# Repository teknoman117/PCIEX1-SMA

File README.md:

# PCIEX1-SMA

Adapts a PCIe x1 slot into 6 SMA connectors (REFCLK, TX, and RX differential pairs), and a pin header for SMBUS and the PERST signal. This is intended to be the one of the lowest cost SMA adapter boards for PCIe x1.

Imagined use case is adapting the Crosslink-NX Evaluation Board into a PCIe capable board by installing the missing SMA connectors and providing an adapter board to an actual PCIe connector.

## License

CC-BY-SA 4.0

## Assembled

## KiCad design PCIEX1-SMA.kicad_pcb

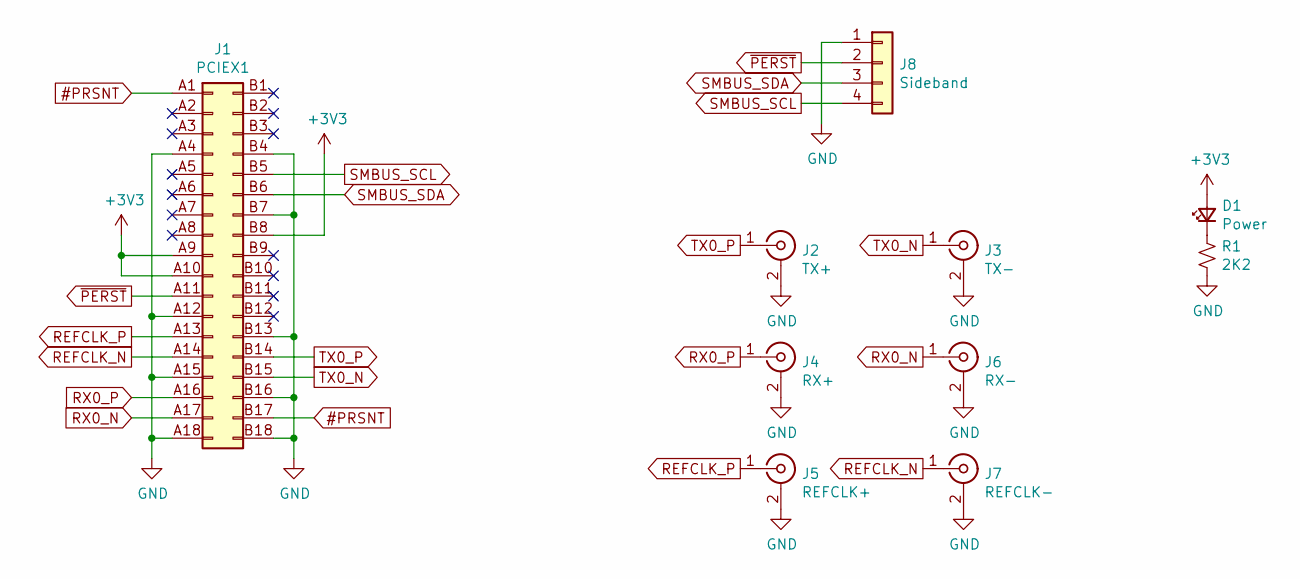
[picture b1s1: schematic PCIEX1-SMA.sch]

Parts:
D1: Power; LED_0603_1608Metric_Pad1.05x0.95mm_HandSolder; Mouser_PN 743-S63BTR
J1: PCIEX1; BUS_PCIexpress_x1
J2: TX+; SMA_Amphenol_132134_Vertical; Mouser_PN 538-73391-0060
J3: TX-; SMA_Amphenol_132134_Vertical
J4: RX+; SMA_Amphenol_132134_Vertical
J5: REFCLK+; SMA_Amphenol_132134_Vertical
J6: RX-; SMA_Amphenol_132134_Vertical
J7: REFCLK-; SMA_Amphenol_132134_Vertical
J8: Sideband; PinHeader_1x04_P2.54mm_Vertical; Mouser_PN 538-42375-2523
R1: 2K2; R_0603_1608Metric_Pad0.98x0.95mm_HandSolder; Mouser_PN 652-CR0603FX-2201ELF

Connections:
#PRSNT: J1.A1 (Pin_a1), J1.B17 (Pin_b17)
+3V3: D1.2 (A), J1.A9 (Pin_a9), J1.A10 (Pin_a10), J1.B8 (Pin_b8)
GND: J1.A4 (Pin_a4), J1.A12 (Pin_a12), J1.A15 (Pin_a15), J1.A18 (Pin_a18), J1.B4 (Pin_b4), J1.B7 (Pin_b7), J1.B13 (Pin_b13), J1.B16 (Pin_b16), J1.B18 (Pin_b18), J2.2 (Ext), J3.2 (Ext), J4.2 (Ext), J5.2 (Ext), J6.2 (Ext), J7.2 (Ext), J8.1, R1.2
unnamed: D1.1 (K), R1.1
REFCLK_N: J1.A14 (Pin_a14), J7.1 (In)
REFCLK_P: J1.A13 (Pin_a13), J5.1 (In)
RX0_N: J1.A17 (Pin_a17), J6.1 (In)
RX0_P: J1.A16 (Pin_a16), J4.1 (In)
SMBUS_SCL: J1.B5 (Pin_b5), J8.4
SMBUS_SDA: J1.B6 (Pin_b6), J8.3
TX0_N: J1.B15 (Pin_b15), J3.1 (In)
TX0_P: J1.B14 (Pin_b14), J2.1 (In)
~PERST: J1.A11 (Pin_a11), J8.2

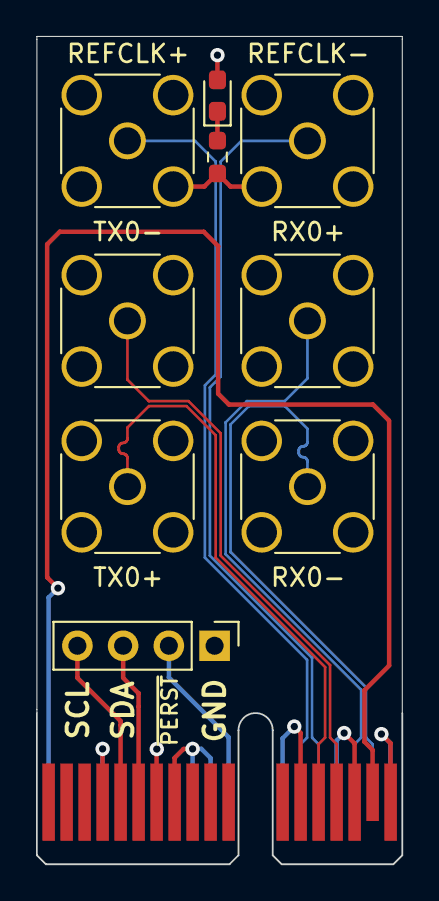
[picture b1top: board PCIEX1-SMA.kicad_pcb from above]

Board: 4 copper layers, 20.3 x 46.0 mm, 10 parts (0 on the bottom side), 13 nets.

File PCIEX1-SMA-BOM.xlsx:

Reference | Quantity | Value | Footprint | Datasheet | Mouser_Link | Mouser_PN
D1 | 1 | Power | LED_SMD:LED_0603_1608Metric_Pad1.05x0.95mm_HandSolder | https://www.mouser.com/datasheet/2/180/IN-S63BT%20Series_V1.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 | https://www.mouser.com/ProductDetail/Inolux/IN-S63BTR?qs=%2F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 | 743-S63BTR
J2 J3 J4 J5 J6 J7 | 1 | (various) | Connector_Coaxial:SMA_Amphenol_132134_Vertical | https://www.mouser.com/datasheet/2/276/1/0733910060_RF_COAX_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 | https://www.mouser.com/ProductDetail/538-73391-0060 | 538-73391-0060
J8 | 1 | Sideband | Connector_PinHeader_2.54mm:PinHeader_1x04_P2.54mm_Vertical | https://www.mouser.com/datasheet/2/276/0423752523_PCB_HEADER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 | https://www.mouser.com/ProductDetail/Molex/42375-2523?qs=ZGc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 | 538-42375-2523
R1 | 1 | 2K2 | Resistor_SMD:R_0603_1608Metric_Pad0.98x0.95mm_HandSolder | https://www.mouser.com/datasheet/2/54/crxxxxx-1858361.pdf | https://www.mouser.com/ProductDetail/Bourns/CR0603-FX-2201EL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 | 652-CR0603FX-2201ELF

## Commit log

2021-09-18 first commit, state at manufacturing
2021-10-04 add assembled pictures
2021-10-28 add picture of link established
